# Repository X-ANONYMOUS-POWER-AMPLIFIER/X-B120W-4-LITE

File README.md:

# X-B120W-4-LITE - SIMPLE MAIN-CIRCUIT MODULE OF 120 WATTS CLASS-B AUDIO POWER AMPLIFIER MAIN-CIRCUIT FOR 4-OHMS OUTPUT LOAD

X-B120W-4-LITE is a power amplifier main-circuit module designed to be simple, with only few number of transistors within its input-stage and its VAS, designed to be fit in a small size single-sided circuit board. It is designed to handle 120 watts of 4-ohms output load power rating.

The circuit of X-B120W-4-LITE applies only the effective circuitry models for each of its blocks. Its input-stage applies a minimalist-but-effective LTP (Long Tailed Pair) circuit model, completed with an active-load and an offset null adjustment trimmer. Its VAS (Voltage Amplifier Stage) applies a simple circuit model but with an advanced active-load technique to achieve high amplification performance, with applies only few number of transistors without needing to apply differential-based topology.

## Advanced VAS Model

The VAS of this power amp main-circuit model has an active load that synchronized with the main VAS side to be working as well a fully symmetrical VAS. The output signal from the LTP buffer (Q4006's emitter) copied by a grounded-base transistor amplifier or signal-current-buffer, Q4008, to feed a copy of signal for VAS's loader, Q4009, makes the VAS's loader to be fully actively working side-by-side with the main VAS, Q4007.

The amplification workflow between LTP buffer, Q4006, into the VAS loader, Q4009, isn't for tackling the DC amplification, but limited for tackling AC amplification. The LTP buffer output, Q4006's emitter, is coupled by C4007 into the emitter of Q4008 for gaining the AC signal only, thus Q4008 can keep its main function as a current-source to provide a constant forward-bias-current for Q4009's base and thus Q4009 also kept its function as a current-source for providing the initial constant forward-bias-current for the output-stage while it is also taking function as an active loader of VAS for providing fully symmetrical AC amplification.

By applying this technique, this power amp main-circuit model will be able to achieve wide headroom even for 1-ohms load in fully symmetrically and certainly achieve high performance in nominal output load (4-ohms or 8-ohms). And certainly, one of the important tings is about limit the number of transistors, makes the X-B120W-4-LITE circuit model quit simple with high performance guarantee.

## Warning: None of Current-Limiter Applied Within The Output-Stage

There is none of current-limiter applied within the output-stage, means that it may introduce a risk of short-circuited output. To prevent a fatal output short-circuited overcome, an output protection circuit have to be applied between the X-B120W-4-LITE module's +SPK output and the loudspeaker. The sensing signal of the overload output or output short-circuit can be obtained via CNT4006.

You may have a question, why none of current-limiter applied within the output-stage? The answer is: Applying the current-limiters within the output-stage, as it commonly applied "just to drop the signal amplitude of the output-stage driver transistor bases" - is not really effective since the VAS will always maintain its signal-current along to follow its amplification level although the current-limiter actives as it detects a short-circuited output.

## License

1. **License Grant**  
The Licensor hereby grants you a worldwide, royalty-free, non-exclusive, perpetual license to use the circuit design for the non-commercial purposes only.
2. **Conditions**  
Attribution: You must provide credit to the original creator when distributing this circuit design.
3. **Disclaimer of Warranty**  
THE DESIGN IS PROVIDED "AS IS". THE LICENSOR MAKES NO WARRANTIES, EXPRESS OR IMPLIED, REGARDING THE DESIGN, INCLUDING BUT NOT LIMITED TO ANY IMPLIED WARRANTIES OF MERCHANTABILITY OR FITNESS FOR A PARTICULAR PURPOSE.
4. **Limitation of Liability**  
IN NO EVENT SHALL THE LICENSOR BE LIABLE FOR ANY DAMAGES, INCLUDING BUT NOT LIMITED TO DIRECT, INDIRECT, INCIDENTAL, OR CONSEQUENTIAL DAMAGES ARISING OUT OF THE USE OF THE DESIGN.

# Design Files Bundle Download

Design files bundle is available for download by follow the URL: [https://github.com/X-ANONYMOUS-POWER-AMPLIFIER/X-B120W-4-LITE/archive/refs/heads/main.zip](https://github.com/X-ANONYMOUS-POWER-AMPLIFIER/X-B120W-4-LITE/archive/refs/heads/main.zip)

The main design files of schematic and PCB design are in [KiCad](https://www.kicad.org/) V.9.x format.

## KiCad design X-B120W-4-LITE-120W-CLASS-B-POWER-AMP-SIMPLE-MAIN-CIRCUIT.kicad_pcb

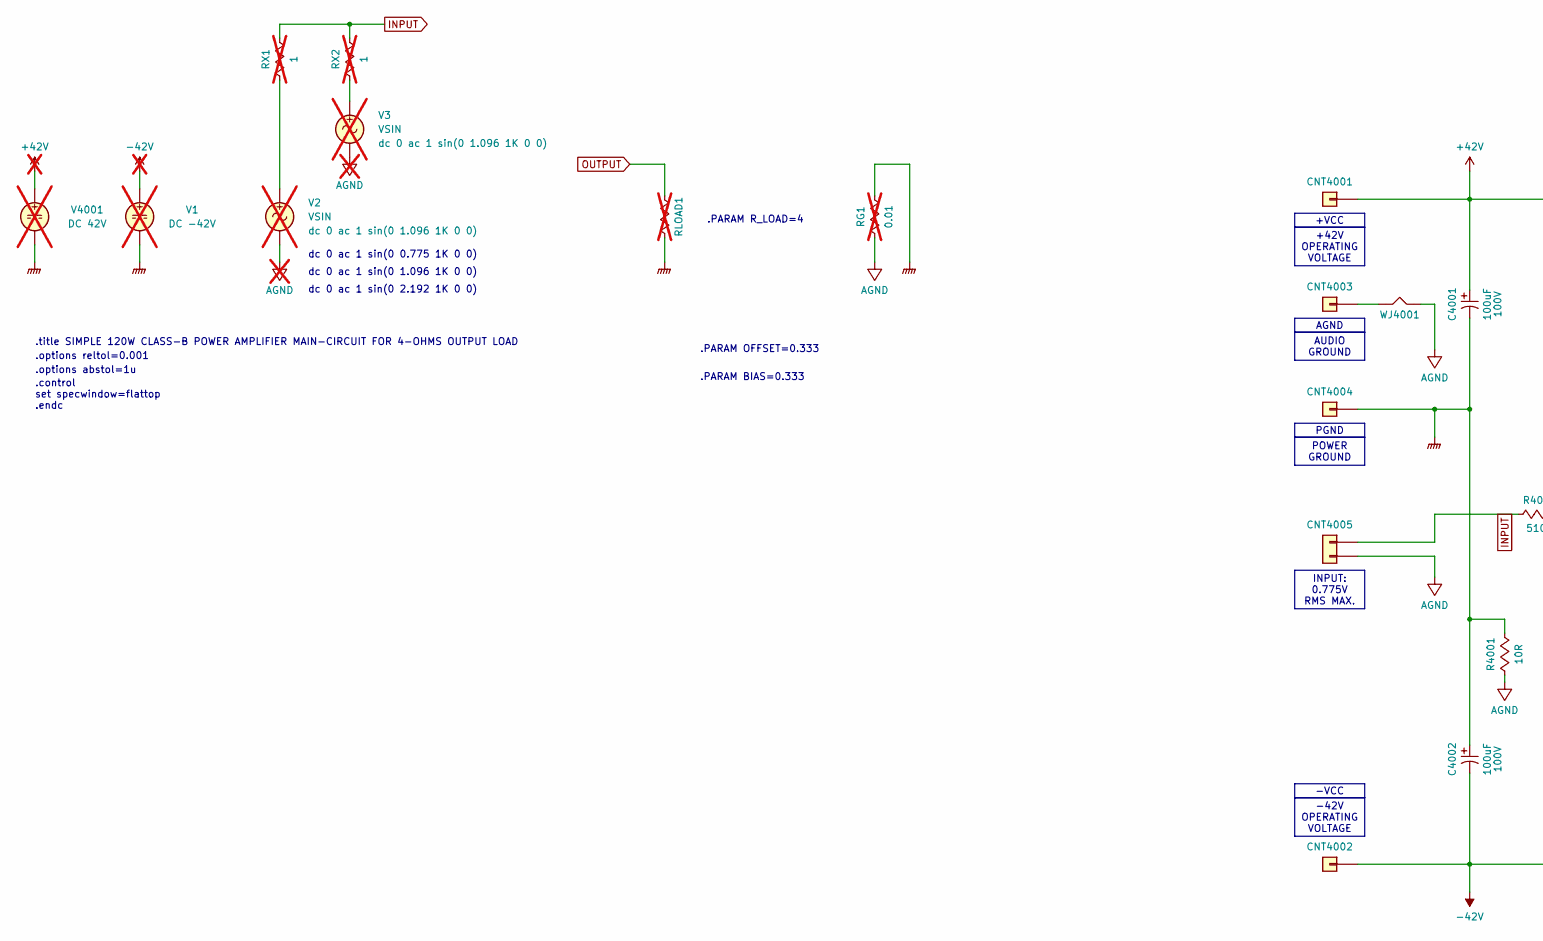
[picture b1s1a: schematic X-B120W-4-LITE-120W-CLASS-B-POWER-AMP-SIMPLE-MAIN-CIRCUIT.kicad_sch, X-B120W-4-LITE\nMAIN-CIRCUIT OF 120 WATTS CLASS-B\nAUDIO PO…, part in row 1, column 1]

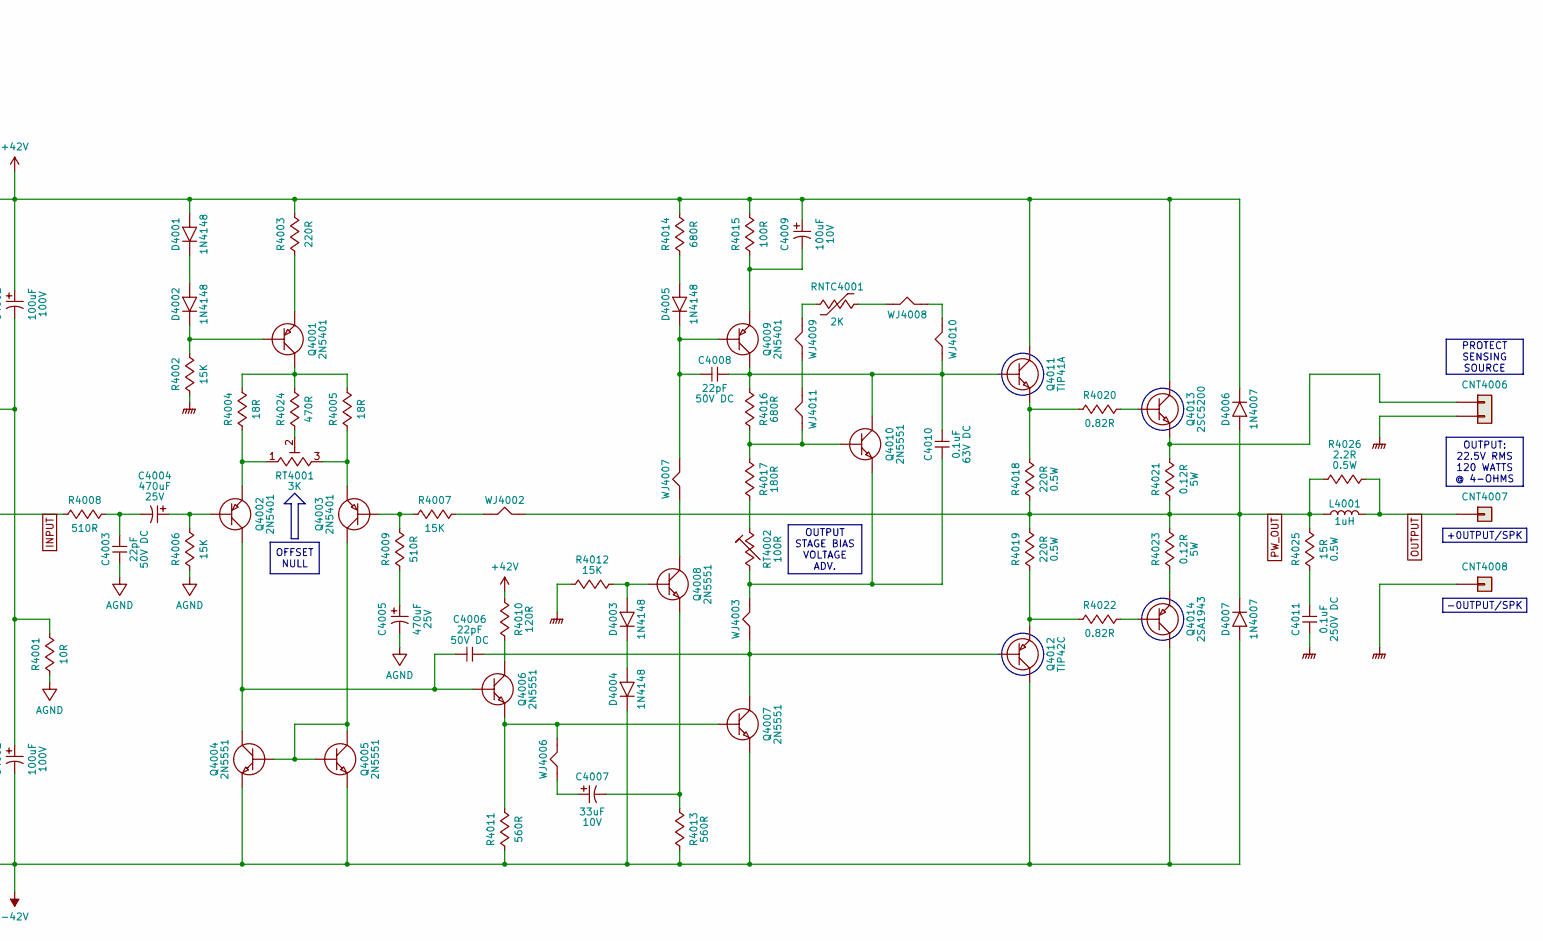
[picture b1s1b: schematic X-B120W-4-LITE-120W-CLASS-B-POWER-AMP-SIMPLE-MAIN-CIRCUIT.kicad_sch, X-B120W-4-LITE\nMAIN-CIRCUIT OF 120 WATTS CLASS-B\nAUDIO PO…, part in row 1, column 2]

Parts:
C4001, C4002: 100uF; CP_Radial_D10.0mm_P5.00mm; Rating 100V
C4003, C4006, C4008: 22pF; C_Disc_D7.5mm_W2.5mm_P5.08mm; Rating 50V DC
C4004, C4005: 470uF; CP_Radial_D8.0mm_P4.00mm_P5.00mm; Rating 25V
C4007: 33uF; CP_Radial_D6.3mm_P2.50mm; Rating 10V
C4009: 100uF; CP_Radial_D6.3mm_P2.50mm; Rating 10V
C4010: 0.1uF; C_Rect_L7.5mm_W2.5mm_P5.00mm_WIMA_MKS2; Rating 63V DC
C4011: 0.1uF; C_Rect_L7.2mm_W4.5mm_P5.00mm_FKS2_FKP2_MKS2_MKP2; Rating 250V DC
CNT4001, CNT4002, CNT4003, CNT4004, CNT4007, CNT4008: 2376582-2; PCB_TAB_250_FASTON_TPBR
CNT4005, CNT4006: 22-27-2021; Molex_KK-254_AE-6410-02A_1x02_P2.54mm_Vertical
D4001, D4002, D4003, D4004, D4005: 1N4148; D_DO-35_SOD27_P10.16mm_Horizontal
D4006, D4007: 1N4007; D_DO-41_SOD81_P10.16mm_Horizontal
L4001: 1uH; Inductor_Air_Core_1uH
Q4001, Q4002, Q4003, Q4009: 2N5401; TO-92_3_Wide
Q4004, Q4005, Q4006, Q4007, Q4008, Q4010: 2N5551; TO-92_3_Wide
Q4011: TIP41A; TO-220-3_Vertical_With_Small_Heatsink
Q4012: TIP42C; TO-220-3_Vertical_With_Small_Heatsink
Q4013: 2SC5200; TO-264-3_Vertical
Q4014: 2SA1943; TO-264-3_Vertical
R4001: 10R; R_Axial_DIN0207_L6.3mm_D2.5mm_P10.16mm; Rating 0.25W
R4002, R4006, R4007, R4012: 15K; R_Axial_DIN0207_L6.3mm_D2.5mm_P10.16mm; Rating 0.25W
R4003: 220R; R_Axial_DIN0207_L6.3mm_D2.5mm_P10.16mm; Rating 0.25W
R4004, R4005: 18R; R_Axial_DIN0207_L6.3mm_D2.5mm_P10.16mm; Rating 0.25W
R4008, R4009: 510R; R_Axial_DIN0207_L6.3mm_D2.5mm_P10.16mm; Rating 0.25W
R4010: 120R; R_Axial_DIN0207_L6.3mm_D2.5mm_P10.16mm; Rating 0.25W
R4011, R4013: 560R; R_Axial_DIN0207_L6.3mm_D2.5mm_P10.16mm; Rating 0.25W
R4014, R4016: 680R; R_Axial_DIN0207_L6.3mm_D2.5mm_P10.16mm; Rating 0.25W
R4015: 100R; R_Axial_DIN0207_L6.3mm_D2.5mm_P10.16mm; Rating 0.25W
R4017: 180R; R_Axial_DIN0207_L6.3mm_D2.5mm_P10.16mm; Rating 0.25W
R4018, R4019: 220R; R_Axial_DIN0309_L9.0mm_D3.2mm_P12.70mm; Rating 0.5W
R4020, R4022: 0.82R; R_Axial_DIN0207_L6.3mm_D2.5mm_P10.16mm; Rating 0.25W
R4021, R4023: 0.12R; R_BPR_5W; Rating 5W
R4024: 470R; R_Axial_DIN0207_L6.3mm_D2.5mm_P10.16mm; Rating 0.25W
R4025: 15R; R_Axial_DIN0309_L9.0mm_D3.2mm_P12.70mm; Rating 0.5W
R4026: 2.2R; R_Axial_DIN0309_L9.0mm_D3.2mm_P12.70mm; Rating 0.5W
RG1: 0.01; R_Axial_DIN0207_L6.3mm_D2.5mm_P10.16mm; Rating 0.25W; not fitted
RLOAD1: r={R_LOAD}; R_Axial_DIN0207_L6.3mm_D2.5mm_P10.16mm; Rating 0.25W; not fitted
RNTC4001: 2K; NTC_D5.0mm_T2.5mm_SP2.50mm_Flip_Mount
RT4001: 3K; Potentiometer_Bourns_3296W_Vertical
RT4002: 100R; Potentiometer_Bourns_3296W_Vertical
RX1, RX2: 1; R_Axial_DIN0207_L6.3mm_D2.5mm_P10.16mm; Rating 0.25W; not fitted
V1: DC -42V; not fitted
V2, V3: VSIN; not fitted
V4001: DC 42V; not fitted
WJ4001, WJ4002: Wire Jumper; J_10.16mm
WJ4003, WJ4006, WJ4007, WJ4008, WJ4009, WJ4010, WJ4011: Wire Jumper; J_12.7mm

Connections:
0: C4001.2, C4002.1, C4011.2, CNT4004.1, CNT4006.2, CNT4008.1, R4001.1, R4002.2, R4012.1, RG1.1, RLOAD1.2, V1.2, V4001.2
+42V: C4001.1, C4009.1, CNT4001.1, D4001.2 (A), D4006.1 (K), Q4011.2 (C), Q4013.2 (C), R4003.1, R4010.1, R4014.1, R4015.1, V4001.1
-42V: C4002.2, CNT4002.1, D4004.1 (K), D4007.2 (A), Q4004.1 (E), Q4005.1 (E), Q4007.1 (E), Q4012.2 (C), Q4014.2 (C), R4011.2, R4013.2, V1.1
AGND: C4003.2, C4005.2, CNT4005.2, R4001.2, R4006.2, RG1.2, V2.2, V3.2, WJ4001.2
INPUT: CNT4005.1, R4008.2, RX1.1, RX2.1
unnamed: C4003.1, C4004.2, R4008.1
unnamed: C4005.1, R4009.2
unnamed: C4007.1, WJ4006.1
unnamed: C4011.1, R4025.2
unnamed: CNT4003.1, WJ4001.1
unnamed: CNT4006.1, Q4013.3 (E), R4021.1
unnamed: D4001.1 (K), D4002.2 (A)
unnamed: D4002.1 (K), Q4001.2 (B), R4002.1
unnamed: D4003.2 (A), Q4008.2 (B), R4012.2
unnamed: D4003.1 (K), D4004.2 (A)
unnamed: D4005.2 (A), R4014.2
unnamed: C4008.2, D4005.1 (K), Q4009.2 (B), WJ4007.2
unnamed: Q4001.3 (C), R4004.1, R4005.1, R4024.1
unnamed: Q4001.1 (E), R4003.2
unnamed: C4004.1, Q4002.2 (B), R4006.1
unnamed: C4006.2, Q4002.3 (C), Q4004.3 (C), Q4006.2 (B)
unnamed: Q4002.1 (E), R4004.2, RT4001.1
unnamed: Q4003.2 (B), R4007.2, R4009.1
unnamed: Q4003.3 (C), Q4004.2 (B), Q4005.2 (B), Q4005.3 (C)
unnamed: Q4003.1 (E), R4005.2, RT4001.3
unnamed: Q4006.3 (C), R4010.2
unnamed: Q4006.1 (E), Q4007.2 (B), R4011.1, WJ4006.2
unnamed: C4006.1, Q4007.3 (C), Q4012.1 (B), WJ4003.2
unnamed: Q4008.3 (C), WJ4007.1
unnamed: C4007.2, Q4008.1 (E), R4013.1
unnamed: C4008.1, C4010.1, Q4009.3 (C), Q4010.3 (C), Q4011.1 (B), R4016.1, WJ4010.1
unnamed: C4009.2, Q4009.1 (E), R4015.2
unnamed: Q4010.2 (B), R4016.2, R4017.1, WJ4011.1
unnamed: C4010.2, Q4010.1 (E), RT4002.2, WJ4003.1
unnamed: Q4011.3 (E), R4018.1, R4020.1
unnamed: Q4012.3 (E), R4019.2, R4022.2
unnamed: Q4013.1 (B), R4020.2
unnamed: Q4014.1 (B), R4022.1
unnamed: Q4014.3 (E), R4023.2
unnamed: R4007.1, WJ4002.1
unnamed: R4017.2, RT4002.1
unnamed: R4024.2, RT4001.2
unnamed: RNTC4001.1, WJ4008.2
unnamed: RNTC4001.2, WJ4009.2
unnamed: RX1.2, V2.1
unnamed: RX2.2, V3.1
unnamed: WJ4008.1, WJ4010.2
unnamed: WJ4009.1, WJ4011.2
OUTPUT: CNT4007.1, L4001.2, R4026.1, RLOAD1.1
PW_OUT: D4006.2 (A), D4007.1 (K), L4001.1, R4018.2, R4019.1, R4021.2, R4023.1, R4025.1, R4026.2, WJ4002.2

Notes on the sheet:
.options abstol=1u
dc 0 ac 1 sin(0 2.192 1K 0 0)
.options reltol=0.001
.title SIMPLE 120W CLASS-B POWER AMPLIFIER MAIN-CIRCUIT FOR 4-OHMS OUTPUT LOAD
dc 0 ac 1 sin(0 0.775 1K 0 0)
.PARAM BIAS=0.333
.PARAM OFFSET=0.333
.PARAM R_LOAD=4
.control set specwindow=flattop .endc
dc 0 ac 1 sin(0 1.096 1K 0 0)
PROTECT SENSING SOURCE
-0UTPUT/SPK
-VCC
INPUT: 0.775V RMS MAX.
POWER GROUND
+VCC
+42V OPERATING VOLTAGE
-42V OPERATING VOLTAGE
OUTPUT: 22.5V RMS 120 WATTS @ 4-OHMS
AUDIO GROUND
+0UTPUT/SPK
PGND
OFFSET NULL
AGND
OUTPUT STAGE BIAS VOLTAGE ADV.

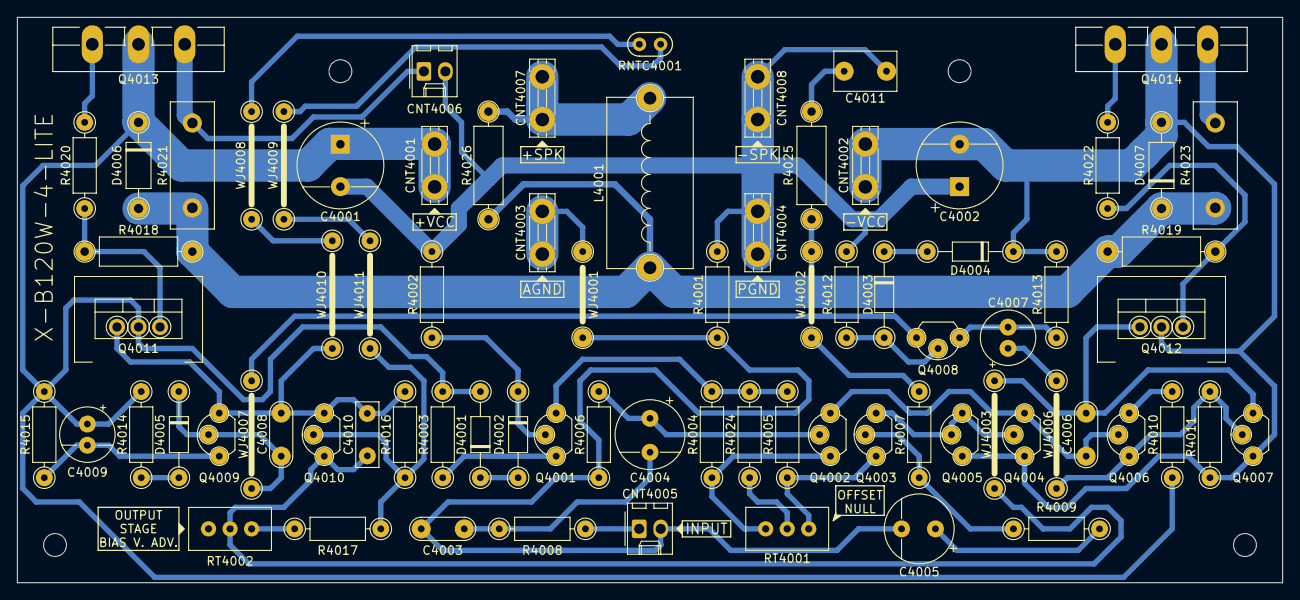
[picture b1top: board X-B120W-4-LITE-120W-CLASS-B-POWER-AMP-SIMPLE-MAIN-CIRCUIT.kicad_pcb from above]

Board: 2 copper layers, 149.2 x 66.7 mm, 79 parts (1 on the bottom side), 48 nets.

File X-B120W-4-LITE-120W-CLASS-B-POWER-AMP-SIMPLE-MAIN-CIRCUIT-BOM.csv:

"Reference","Value","Rating","Description","MFR Number","Manufacturer","Qty"
"C4001,C4002","100uF","100V","Aluminum Electrolytic Capacitors - Radial Leaded 100uF 100V","ECA-1EM100I ","Panasonic","2"
"C4003,C4006,C4008","22pF","50V DC","Multilayer Ceramic Capacitors MLCC - Leaded 22PF 50V 5% 5.0MM","RDE5C1H220J0K1H03B","Murata","3"
"C4004,C4005","470uF","25V","Aluminum Electrolytic Capacitors - Radial Leaded 470uF 25V","EEU-FC1E471L","Panasonic","2"
"C4007","33uF","10V","Aluminum Electrolytic Capacitors - Radial Leaded 10VDC 33uF POLARIZED","ECE-A1AKS330I","Panasonic","1"
"C4009","100uF","10V","Aluminum Electrolytic Capacitors - Radial Leaded 100uF 10V","ECE-A1AKA101","Panasonic","1"
"C4010","0.1uF","63V DC","Film Capacitors 0.1 uF 63 VDC 5%","MKS2C031001A00JI00","WIMA","1"
"C4011","0.1uF","250V DC","Film Capacitors 0.1 uF 250 VDC 20%","MKS2F031001E00MSSD ","WIMA","1"
"CNT4001,CNT4002,CNT4003,CNT4004,CNT4007,CNT4008","2376582-2","","250 FASTON PCB TAB TPBR","2376582-2","TE Connectivity","6"
"CNT4005,CNT4006","22-27-2021","","Headers & Wire Housings 2 POS HEADER","22-27-2021","Molex","2"
"D4001,D4002,D4003,D4004,D4005","1N4148","","Small Signal Switching Diodes Small Signal Diode, DO-35, 100V, 0.2A, 175C","1N4148","Diotec Semiconductor","5"
"D4006,D4007","1N4007","","Rectifiers Diode, DO-41, 1000V, 1A","1N4007","Diotec Semiconductor","2"
"L4001","1uH","","Air Core Inductor, 16 windings, D = 8 mm, enameled wire diameter = 1.2 mm","","","1"
"Q4001,Q4002,Q4003,Q4009","2N5401","","Bipolar Transistors - BJT PNP 160Vcbo 150Vceo 5.0Vebo 600mA 625mW","2N5401 TIN/LEAD","Central Semiconductor ","4"
"Q4004,Q4005,Q4006,Q4007,Q4008,Q4010","2N5551","","Bipolar Transistors - BJT NPN 180Vcbo 160Vceo 6.0Vebo 600mA 625mW\","2N5551 TIN/LEAD","Central Semiconductor ","6"
"Q4011","TIP41A","","Bipolar Transistors - BJT 6A 100V 65W NPN","TIP41C","STMicroelectronics ","1"
"Q4012","TIP42C","","Bipolar Transistors - BJT 6A 100V 65W PNP","TIP42C","STMicroelectronics ","1"
"Q4013","2SC5200","","Bipolar Transistors - BJT NPN 230V 15A","2SC5200-O(Q)","Toshiba","1"
"Q4014","2SA1943","","Bipolar Transistors - BJT PNP 230V 15A","2SA1943-O(Q)","Toshiba","1"
"R4001","10R","0.25W","Metal Film Resistors - Through Hole 10 OHM 1/4W 1%","MFR-25FRE52-10R","YAGEO","1"
"R4002,R4006,R4007,R4012","15K","0.25W","Metal Film Resistors - Through Hole 15K OHM 1/4W 1%","MFR-25FRE52-15K","YAGEO","4"
"R4003","220R","0.25W","Metal Film Resistors - Through Hole 220 OHM 1/4W 1%","MFR-25FRE52-220R","YAGEO","1"
"R4004,R4005","18R","0.25W","Metal Film Resistors - Through Hole 18 OHM 1/4W 1%","MFR-25FRE52-18R","YAGEO","2"
"R4008,R4009","510R","0.25W","Metal Film Resistors - Through Hole 510 OHM 1/4W 1%","MFR-25FRE52-510R","YAGEO","2"
"R4010","120R","0.25W","Metal Film Resistors - Through Hole 120 OHM 1/4W 1%","MFR-25FRE52-120R","YAGEO","1"
"R4011,R4013","560R","0.25W","Metal Film Resistors - Through Hole 560 OHM 1/4W 1%","MFR-25FRE52-560R","YAGEO","2"
"R4014,R4016","680R","0.25W","Metal Film Resistors - Through Hole 680 OHM 1/4W 1%","MFR-25FRE52-680R","YAGEO","2"
"R4015","100R","0.25W","Metal Film Resistors - Through Hole 100 OHM 1/4W 1%","MFR-25FRE52-100R","YAGEO","1"
"R4017","180R","0.25W","Metal Film Resistors - Through Hole 180 OHM 1/4W 1%","MFR-25FRE52-180R","YAGEO","1"
"R4018,R4019","220R","0.5W","Metal Film Resistors - Through Hole 220 OHM 1/5W 1%","MFR-50FTE52-220R","YAGEO","2"
"R4020,R4022","0.82R","0.25W","Metal Oxide Resistors RSS1/2 .82 5%TR","MOSX1/2CT52RR82J ","KOA Speer","2"
"R4021,R4023","0.12R","5W","Current Sense Resistors - Through Hole 0.12 Ohm 5W 5% 350ppm","BPR58CR12J","KOA Speer","2"
"R4024","470R","0.25W","Metal Film Resistors - Through Hole 510 OHM 1/4W 1%","MFR-25FRE52-510R","YAGEO","1"
"R4025","15R","0.5W","Metal Film Resistors - Through Hole 15 OHM 1/5W 1%","MFR-50FTE52-15R","YAGEO","1"
"R4026","2.2R","0.5W","Metal Film Resistors - Through Hole 2.2 OHM 1/5W 1%","MFR-50FTE52-2R2","YAGEO","1"
"RNTC4001","2K","","NTC Thermistors 2Kohm/2% 3528/0.5%","NTCLE100E3202GB0A","Vishay / BC Components","1"
"RT4001","3K","","Trimmer Resistors - Through Hole 3/8"" 3Kohms Sealed Vertical Adjust","3296W-1-302ALF","Bourns","1"
"RT4002","100R","","Trimmer Resistors - Through Hole 3/8"" 100 ohms Sealed Vertical Adjust","3296W-1-101ALF","Bourns","1"
"WJ4001,WJ4002,WJ4003,WJ4006,WJ4007,WJ4008,WJ4009,WJ4010,WJ4011","Wire Jumper","","Wire Jumper","","","9"
